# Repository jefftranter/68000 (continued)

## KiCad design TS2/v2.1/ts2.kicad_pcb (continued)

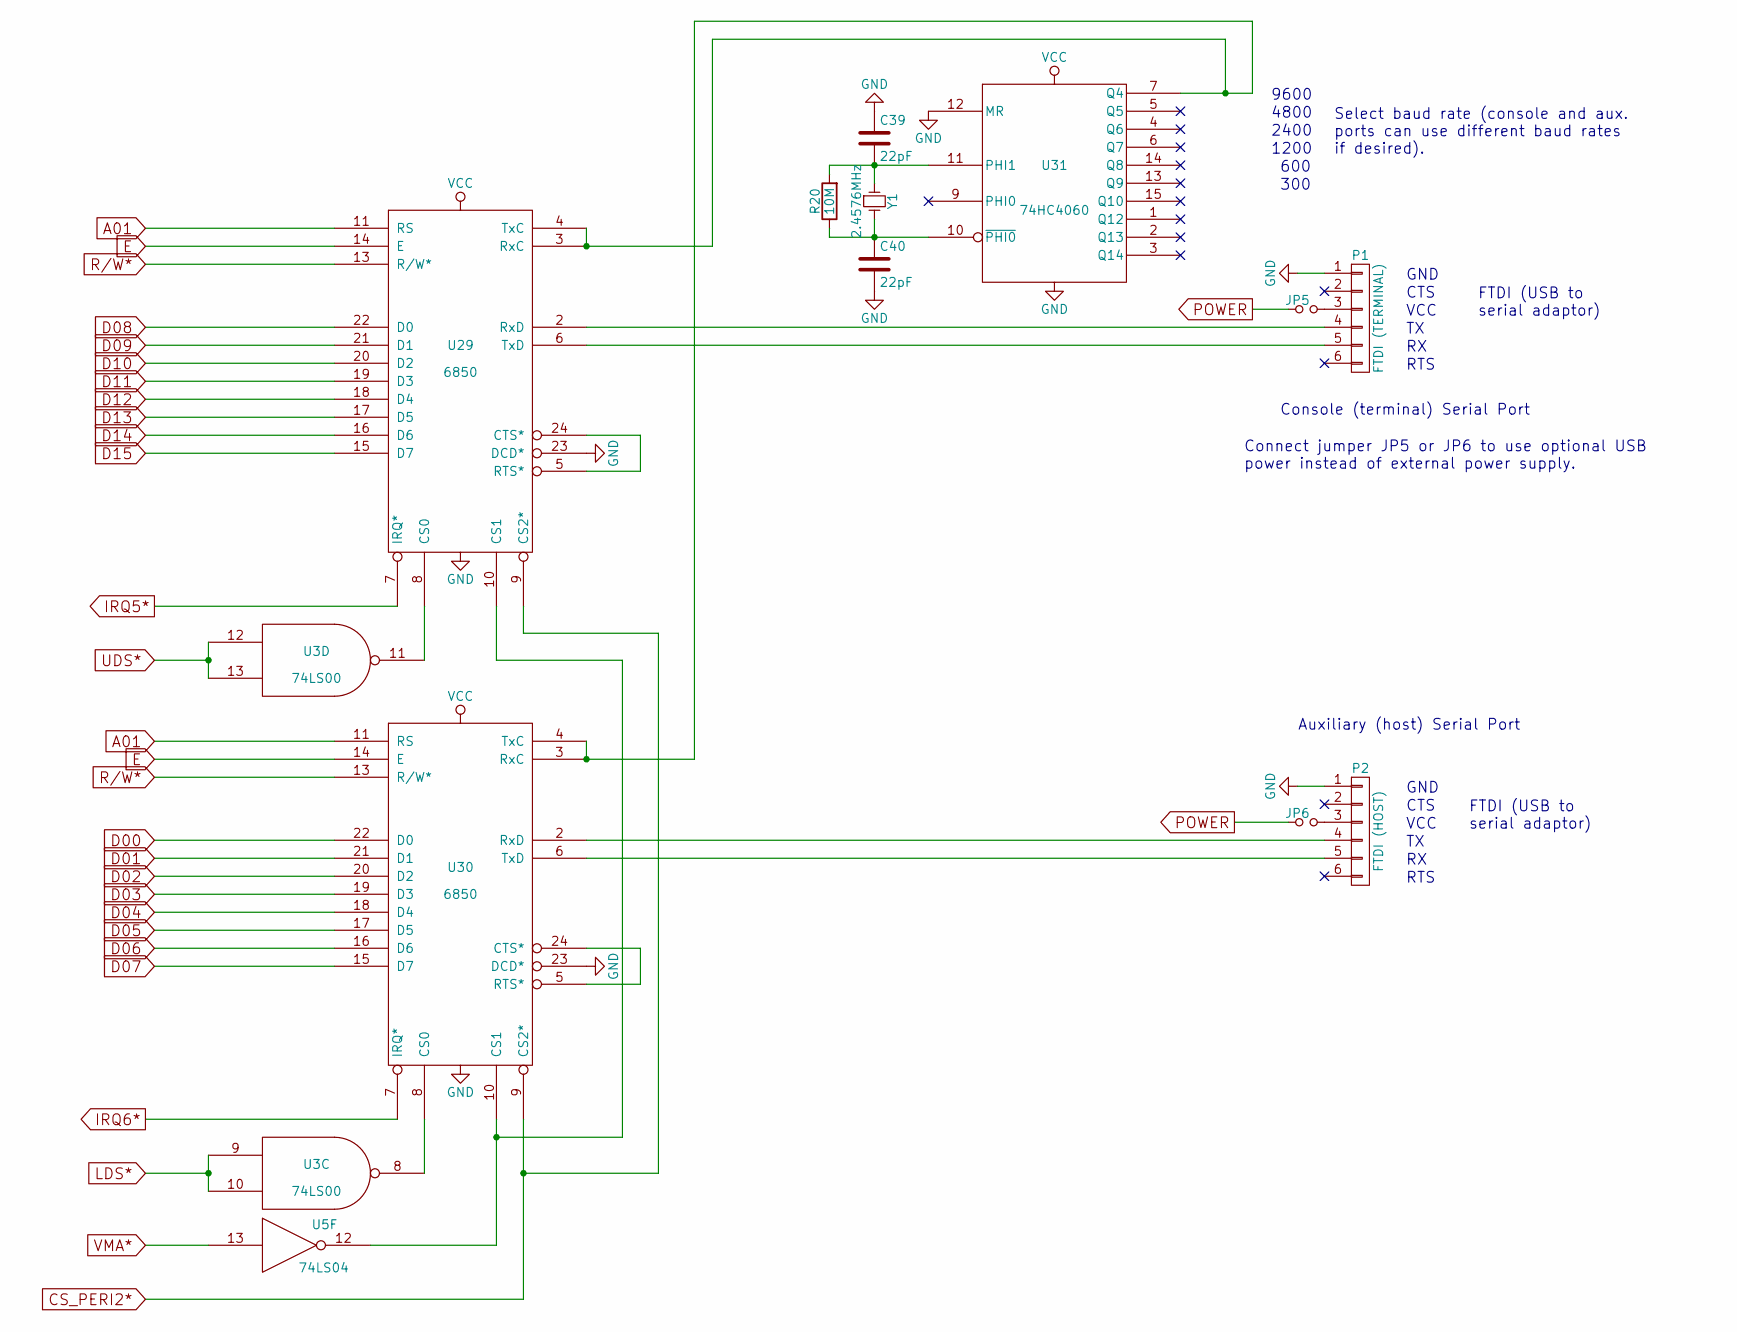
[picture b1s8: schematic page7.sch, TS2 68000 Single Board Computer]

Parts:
C39, C40: 22pF; C_Disc_D3_P2.5
JP5, JP6: Jumper_NO_Small; PINHEAD1-2
P1: FTDI (TERMINAL); PINHEAD1-6
P2: FTDI (HOST); PINHEAD1-6
R20: 10M; Resistor_Horizontal_RM7mm
U3: 74LS00; DIP-14_W7.62mm
U5: 74LS04; DIP-14_W7.62mm
U29, U30: 6850; DIP-24_W15.24mm
U31: 74HC4060; DIP-16_W7.62mm
Y1: 2.4576MHz; Crystal_HC49-U_Vertical

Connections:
A01: U29.11 (RS), U30.11 (RS); also elsewhere on the board
CS_PERI2*: U29.9 (CS2*), U30.9 (CS2*); also elsewhere on the board
D00: U30.22 (D0); also elsewhere on the board
D01: U30.21 (D1); also elsewhere on the board
D02: U30.20 (D2); also elsewhere on the board
D03: U30.19 (D3); also elsewhere on the board
D04: U30.18 (D4); also elsewhere on the board
D05: U30.17 (D5); also elsewhere on the board
D06: U30.16 (D6); also elsewhere on the board
D07: U30.15 (D7); also elsewhere on the board
D08: U29.22 (D0); also elsewhere on the board
D09: U29.21 (D1); also elsewhere on the board
D10: U29.20 (D2); also elsewhere on the board
D11: U29.19 (D3); also elsewhere on the board
D12: U29.18 (D4); also elsewhere on the board
D13: U29.17 (D5); also elsewhere on the board
D14: U29.16 (D6); also elsewhere on the board
D15: U29.15 (D7); also elsewhere on the board
E: U29.14 (E), U30.14 (E); also elsewhere on the board
GND: C39.1, C40.2, P1.1, P2.1, U3.7 (GND), U5.7 (GND), U29.1 (GND), U29.23 (DCD*), U30.1 (GND), U30.23 (DCD*), U31.8 (GND), U31.12 (MR); also elsewhere on the board
IRQ5*: U29.7 (IRQ*); also elsewhere on the board
IRQ6*: U30.7 (IRQ*); also elsewhere on the board
LDS*: U3.9, U3.10; also elsewhere on the board
unnamed: C39.2, R20.2, U31.11 (PHI1), Y1.1
unnamed: C40.1, R20.1, U31.10 (~PHI0), Y1.2
unnamed: JP5.2, P1.3
unnamed: JP6.2, P2.3
unnamed: P1.4, U29.2 (RxD)
unnamed: P1.5, U29.6 (TxD)
unnamed: P2.4, U30.2 (RxD)
unnamed: P2.5, U30.6 (TxD)
unnamed: U3.8, U30.8 (CS0)
unnamed: U29.3 (RxC), U29.4 (TxC), U30.3 (RxC), U30.4 (TxC), U31.7 (Q4)
unnamed: U3.11, U29.8 (CS0)
unnamed: U5.12, U29.10 (CS1), U30.10 (CS1)
unnamed: U29.5 (RTS*), U29.24 (CTS*)
unnamed: U30.5 (RTS*), U30.24 (CTS*)
POWER: JP5.1, JP6.1; also elsewhere on the board
R/W*: U29.13 (R/W*), U30.13 (R/W*); also elsewhere on the board
UDS*: U3.12, U3.13; also elsewhere on the board
VMA*: U5.13; also elsewhere on the board

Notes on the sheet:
GND
CTS
VCC
RTS
9600
4800
2400
1200
600
300
Select baud rate (console and aux. ports can use different baud rates if desired).
FTDI (USB to serial adaptor)
Auxiliary (host) Serial Port
Console (terminal) Serial Port
Connect jumper JP5 or JP6 to use optional USB power instead of external power supply.

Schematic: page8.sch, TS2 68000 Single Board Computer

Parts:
RR1: 4.7K; Resistor_Array_SIP8
SW4: ABORT; PINHEAD1-3
U4: 74LS06; DIP-14_W7.62mm
U7: 74LS08; DIP-14_W7.62mm
U28: 74LS148; DIP-16_W7.62mm
U32, U33: 74LS138; DIP-16_W7.62mm
U34: 74LS00; DIP-14_W7.62mm
U35: 74LS74; DIP-14_W7.62mm
U37: 74LS00

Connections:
/page8/IACK3*: U7.9, U33.11 (O4)
/page8/IACK5*: U7.10, U33.10 (O5)
/page8/IACK6*: U7.12, U33.9 (O6)
/page8/IACK7*: U7.13, U33.7 (O7), U35.1 (Cd)
A01: U33.1 (A0); also elsewhere on the board
A02: U33.2 (A1); also elsewhere on the board
A03: U33.3 (A2); also elsewhere on the board
FC0: U32.1 (A0); also elsewhere on the board
FC1: U32.2 (A1); also elsewhere on the board
FC2: U32.3 (A2); also elsewhere on the board
GND: SW4.2, U4.7 (GND), U7.7 (GND), U28.5 (EI), U28.8 (GND), U28.10 (IO), U32.4 (E1), U32.5 (E2), U32.8 (GND), U33.8 (GND), U34.7 (GND), U35.7 (GND), U37.7 (GND); also elsewhere on the board
IPL0*: U28.9 (S0); also elsewhere on the board
IPL1*: U28.7 (S1); also elsewhere on the board
IPL2*: U28.6 (S2); also elsewhere on the board
IRQ1*: RR1.2, U28.11 (I1)
IRQ2*: RR1.3, U28.12 (I2)
IRQ3*: RR1.4, U28.13 (I3)
IRQ4*: RR1.5, U28.1 (I4)
IRQ5*: RR1.6, U28.2 (I5); also elsewhere on the board
IRQ6*: RR1.7, U28.3 (I6); also elsewhere on the board
IRQ7*: U28.4 (I7), U35.6 (~Q)
unnamed: RR1.8, SW4.3, U34.5
unnamed: RR1.9, SW4.1, U34.1
unnamed: U32.7 (O7), U33.4 (E1)
unnamed: U34.2, U34.6, U35.3 (Cp)
unnamed: U34.3, U34.4
unnamed: U34.8, U37.9, U37.10
unnamed: U7.8, U34.9
unnamed: U7.11, U34.10
unnamed: U4.13, U34.11
unnamed: U34.12, U37.8
PERI_VPA*: U34.13; also elsewhere on the board
VPA*: U4.12; also elsewhere on the board

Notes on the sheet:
7 levels of interrupt request
7 levels of interrupt acknowledge
IACK*
Function codes 0-7

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
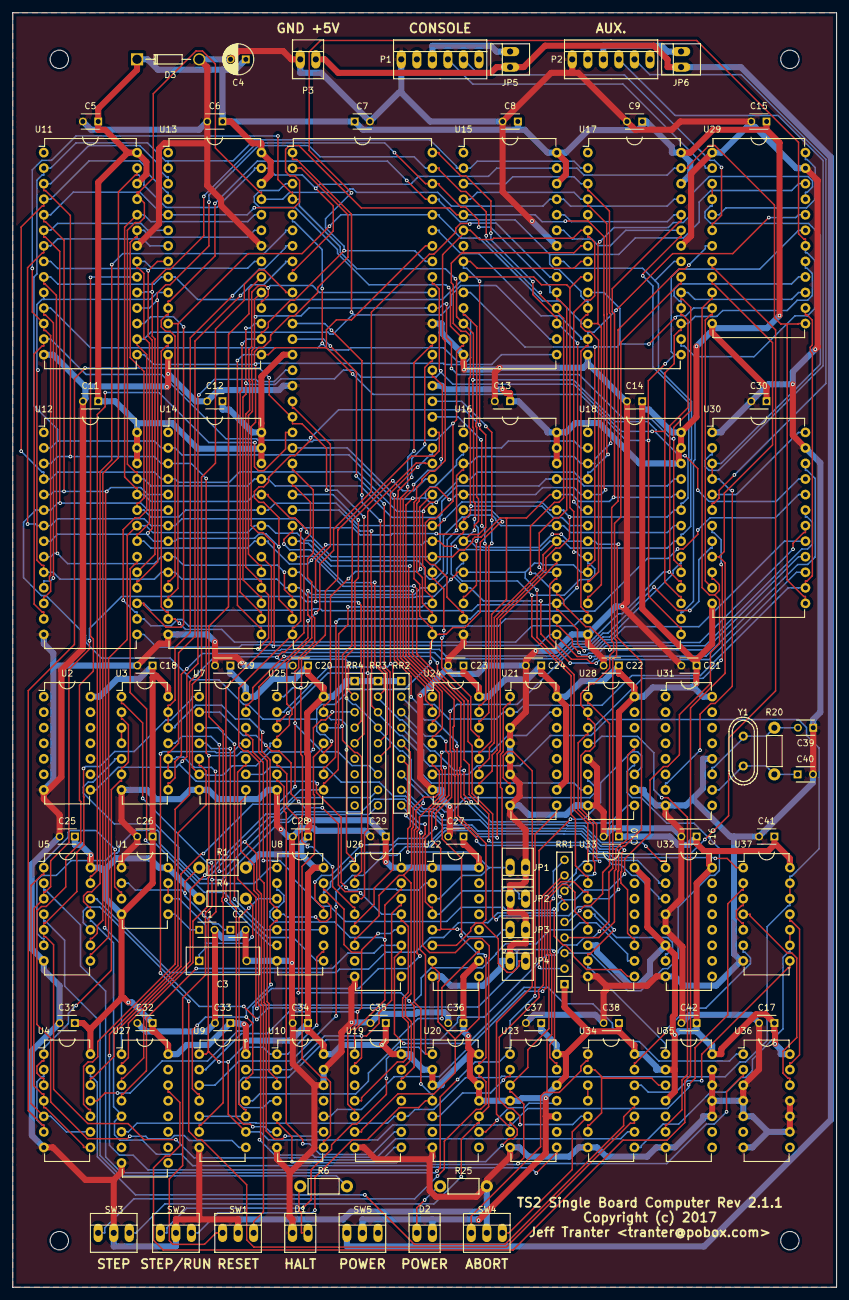
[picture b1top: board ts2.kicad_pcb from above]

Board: 2 copper layers, 134.6 x 208.3 mm, 110 parts (0 on the bottom side), 155 nets.

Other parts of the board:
HOLE1, HOLE2, HOLE3, HOLE4: MountingHole_3mm

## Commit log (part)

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2017-05-21 Add more examples.
2017-05-21 Check in some more files.
2017-05-22 Add index of examples.
2017-05-22 Add exception example.
2017-05-22 Add C example.
2017-05-22 Minor updates.
2017-05-23 Expand example to do some output.
2017-05-24 Better printNumber routine.
2017-05-24 Make some corrections.
2017-05-29 Update after build PCB.
2017-05-29 Add note for 2.2.1 version.
2017-05-31 Add some floating point code and link with 68000 version of libgcc.
2017-05-31 Add misc. notes.
2017-05-31 Rev 2.1.1 changes.
2017-06-02 Remove extraneous node.
2017-06-04 Start of example using newlib.
2017-06-07 Check in files for building gcc and newlib.
2017-06-07 Update example.
2017-06-08 Use better name for build dir.
2017-06-09 Remove some extra blank lines.
2017-06-09 Add some more info.
2017-06-10 Add some more detail on cover, etc.
2017-06-12 Add another example. Echo character input.
2017-06-17 Add top level make file. Use quiet option when assembling.
2017-07-03 Start of a new program.
2017-07-03 Implement more functionality.
2017-07-04 Factor out crlf routine.
2017-07-04 Implement stack push.
2017-07-04 Print stack using current base.
2017-07-04 Formatting.
2017-07-04 Start implementing hex input.
2017-07-04 Implementing hex input.
2017-07-04 1's complement and 2's complement.
2017-07-04 Handle overflow and some other cleanup.
2017-07-04 Add error checking and support for lowercase hex characters.
2017-07-05 Handle decimal number with leading minus sign.
2017-07-05 Optimize short branches.
2017-07-05 Optimize add.
2017-07-05 Implement 32-bit divide and remainder.
2017-07-06 Implement some FORTH commands.
2017-07-06 Change stack command to dot, implement comparison operator, add missing commands to help.
2017-07-08 Check in files for Quelo example.
2017-07-09 Check in initial files.
2017-07-09 Add comment on usage, remove some unused variables.
2017-07-10 Add example of extending TUTOR trap functions.
2017-07-10 Make some small improvements.
2017-07-13 Start new program.
2017-07-14 Update to reflect game,
2017-07-14 Almost there.
2017-07-15 Bug fixes. Seems to be working now.
2017-07-15 Better handling or random range limits.
2017-07-15 Improve random routine.
2017-07-15 Better initialization of random seed.
2017-07-15 Implement Spock Lizard variation.
2017-07-15 List reason for each winning play.
2017-07-15 Clean up table.
2017-07-15 Add recent projects to top level make file.
2017-07-16 Simplify code by using lookup table.
2017-07-16 Make code position independent.
2017-07-16 Fix PIC bug.
2017-07-18 Set random seed by incrementing counter and waiting for user to press key.
2017-07-18 Fix indentation error.
2017-07-18 Optimize some moves and branches.
2018-06-17 Minor updates and corrections.
2018-06-19 Add a possible future enhancement.
2018-07-06 Correct some BOM errors.
2019-07-16 Check in listing and run files for programs that go into ROM.
2019-07-30 Generate Intel hex files and check them in as well as binary ROM files.
2019-09-23 Fix warning in make file.
2019-10-24 Start of disassembler program.
2019-10-24 Start with some code to read the CSV file.
2019-10-26 Add more code.
2019-10-27 More prototyping.
2019-10-27 Use a different a simpler table format.
2019-10-28 Implement Bcc instructions.
2019-10-28 Implement EORI to CCR and SR.
2019-10-28 EXT.
2019-10-29 Implement MOVE USP.
2019-10-29 Implement DBcc.
2019-10-29 Implement MOVEQ.
2019-10-30 Implement SBCD.
2019-10-30 Implement EXG.
2019-10-31 Implement ADDX.
2019-10-31 Implement SUBX.
2019-10-31 Implementing JMP and JSR.
2019-10-31 Implementing ORI and related instructions.
2019-11-01 Implementing ORI for .L.
2019-11-02 Add more test instructions.
2019-11-02 Rename test program, start on BTST.
2019-11-02 Start on BTST.
2019-11-02 Implement BTST.
2019-11-02 Add BCRL, BCHG, and BSET.
2019-11-02 Implement TST.
2019-11-12 Add more instructions.
2019-11-13 Implement MOVE to CCR, MOVE to/from SR.
2019-11-13 Implement PEA and TAS.
2019-11-13 Handle more shift and rotate instructions.
2019-11-15 Implement ADDA, CMPA, SUBA.
2019-11-15 Implementing MOVEM.
2019-11-15 Implement regsister lists for MOVEM.
2019-11-16 Factor out common code into procedure.
2019-11-17 Implementing MOVE.
2019-11-17 Implement LEA and CHK.
2019-11-17 Implement Scc.
2019-11-17 Implement MUL and DIV.
2019-11-17 Implement CMP and EOR.
2019-11-18 Clean up error messages, implement -n option.
2019-11-19 Refactor common code and misc. tweaking.
2019-11-23 Change M68K opcode table URL
    The link to that nicely organised 68000 opcode table no longer works.
    Two working alternatives are suggested.
2019-12-06 Indentation fix.
2019-12-21 Try to fix formatting.
2020-01-05 Implement size in address with index addressing mode.
2020-01-05 Fix bug with MOVE imm long.
2020-01-06 Fix for OR.
2020-01-06 Fix for MOVE #.
2020-01-06 Fix for MOVE.
2020-01-07 Use signed values for MOVEQ.
2020-01-07 more fixes and tweaks and improved test program. Verify disassembled output assembled back to original code.
2020-01-08 Improvement.
2020-04-08 added: drdobbs 1985 volume 10 links
2020-08-17 Bump version to 3.53.
2020-08-24 Add some porting tips.
2020-08-29 Add port of games.
2020-10-04 Experimental patches to support SAVE and LOAD using a Hobbytronics USB Flash Drive.
2020-10-05 Fix typo.
2020-10-17 Fix typo in comment.
2020-10-18 Add interrupt driven input example.
2020-10-18 Add check for end of buffer.
2020-10-20 Bug fixes.
2020-10-22 Bug fix.
2020-10-24 add export settings
2020-10-24 add gerber & drill combined zip file
2020-10-24 add PCB manufacturing instructions, specify used export settings
2020-10-24 fix typo
2020-10-25 LOAD is working some of the time, needs more debugging.
2020-10-25 Remove redundant echo.
2020-10-25 Adds support for filename on SAVE.
2020-10-27 Support for entering filename for LOAD.
2020-10-28 Disable Control-C check when input comes fromflash card.
2020-10-31 Optimizing delay.
2020-10-31 Support for Backspace/Delete.
2020-11-01 Cuplrit for corrupted data was Basic 18C3 routine. Works if I avoid it.
2020-11-01 Added my own string output routines.
2020-11-01 No longer need to modify Control-C check during LOAD/SAVE.
2020-11-01 Make LOAD/SAVE conditionalty assembled.
2020-11-01 Suppress harmless signed/unsigned warnings.
2020-11-01 Makefile changes for newer GNU assembler version.
2020-11-06 Add silkscreen DIP orientation marks
2020-11-11 Don't commit intermediate C compilation files, intermediate Python and Jetbrains IDE stuff
2020-11-11 fix table layout
2020-11-11 fix list layout
2020-11-11 add advice to use soldering flux
2020-11-16 add list of dependencies for pipenv
2020-11-16 fix Makefile, add install action to install python dependencies
2020-11-16 ignore vasm sources and compiled binaries
2020-11-16 update usage instructions
2020-11-16 fine-tune install script: use more reliable wget download strategy
2020-11-19 move pipenv install to separate line
2020-11-21 Increase max line length to prevent pystyle errors.
2020-11-21 combine minipro software building in single recipe
2020-11-21 fix missing ./ path specifier
2020-11-21 compiling gcc isn't exactly trivial
2020-11-22 working recipe for building and installing gcc cross compiler
2020-11-22 use Makefile-idiomatic conditionals to check for pkg-config and libusb, add minipro write commands to write data to ROM
2020-11-23 fix checking for connected minipro and installed gawk
2020-11-24 add recipe for simple s-record tools
2020-11-24 simplify recipes for rom writing
2020-11-25 fix srec install: check for installed unzip
2020-11-25 Add binary odd/even files and Makefile rules.
2020-11-26 remove now-redundant entries for vasm and tutor: they are no longer pulled into the git repo dir
2020-11-26 add toolchain recipes for srec, gcc cross compiler, minipro CLI, vasm assembler
2020-11-26 move disassembler into toolchain directory
2020-11-26 make most target directories configurable
2020-11-26 add description of Srec programs
2020-11-26 add generic install config options, add GCC cross compiler section
2020-11-26 make binary install dir configurable, remove redundant srec variables, replace hard-coded bin dir paths with variables
2020-11-26 add usage instructions for gcc
2020-11-28 add uninstall recipe for srec
2020-11-28 add uninstall recipe for gcc, add documentation
2020-11-28 substitute all binary install dir references with install dirs for ease of use and understandability
2020-11-28 ad srec_cat install test, use INSTALL_DIR as prefix for gcc configuration
2020-11-29 include installation of cross-compile binutils
2020-11-29 don't remove gcc build dir, it may contain libgcc.a which is needed by binutils m68k-elf-ld
2020-11-29 build libgcc, clean up afterwards
2020-11-30 move newlib patches into toolchain dir
2020-11-30 refine documentation on usage of ~/.local, add newlib description
2020-11-30 refactor install shell script into Makefile
2020-11-30 add documentation reference to newlib folder README.md
2020-12-05 add uninstall target for newlib
2020-12-05 add targets for installation and de-installation of disassembler
2020-12-05 add disassembler instructions
2020-12-05 finish vasm (un)install and instructions
2020-12-16 Add some more text to clarify use of jumpers.
2022-07-26 Start adding game backup/restore feature.
2022-07-28 Implementing backup/restore to file.
2022-07-28 Remove debugging output.
2022-07-29 Implement backup/restore comments for Adventure2.
2022-07-29 Make command usage consistent.
2022-08-14 Tweaks to build scripts.
2022-09-07 Fix small typo in memory map document.
2022-09-13 Fix line endings.
2022-09-13 Add support for running out of ROM.
2022-10-16 Fix some small issues.
2022-10-18 Change to match 6502 cc65 version.
2022-10-29 Enable file i/o on platforms where it is supported.
2022-10-31 Update versions of tools used.
2022-11-04 Fix small typo.
2022-11-04 Change decimal command to 'd'.
2022-11-04 Revert previous change.
2023-01-01 Add first version of new adventure game.
2023-01-01 Allow abbreviating an item name as long as it is a unique match.
2023-03-20 Update some info.
2023-03-21 Some small improvements.
2023-03-21 Remove duplicated lines.
2023-03-22 Small improvements.
2023-03-23 Small improvements,.
2023-03-23 Documentation updates. Add support for newlib-nano. Add another C example program.
2023-03-26 Some make file cleanup.
2023-04-17 Clarify some connector designations.
2023-04-22 Update PDF version of BOM.
2024-01-06 Fix typo in readme file.
2024-01-06 Update paths for building.
2024-01-06 add upload rule.
2024-01-06 Just for fun, add square root functions using external square root code.
2024-01-06 Fix typo in Makefile comment.
2024-01-07 Update versions to build.
2024-01-07 Fix FADDR macro so it can be used and avoid manually updating lookup table addresses.
2024-03-28 Fix link to TAPR license.
2024-08-22 Fix some spelling errors in source code comments.
2025-01-07 Remove imvalid test cases and fix up make file.
2025-01-07 Update to latest versions of tools.
2025-09-28 Make various fixes.
2025-09-28 Remove PC relative test cases as the work differently with assembler being used.
2025-09-29 Fix issue #12: Show byte size immediate values as 8 bits and not 16.
2026-01-04 Latest assembler generates slightly different code (optimization).
2026-03-11 Array can be 10 entries rather than 11. Thanks to <pollo1985@protonmail.com> for pointing this out.
2026-03-12 removed unnecessay nested function
2026-03-12 Fix some formatting issues to comply with Python style standards.
2026-03-12 Make some corrections to the README.md file.
2026-03-31 Show illegal instructions as ILLEGAL.
2026-03-31 Add -w option to control warnings.
2026-03-31 Revert previous changes as they broke some disassembkly. Address issue #14 by initializing a variable.
2026-04-20 Remove unneeded and misleading line of code that refers to non-existent error 5.
2026-05-14 Move the csv table into a python file as described in the to do list in comments. Does not remove any unused coloumns.
